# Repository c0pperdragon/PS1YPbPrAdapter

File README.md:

# PS1 YPbPr Adapter

## Goal

To get the best possible image quality from the original Sony Playstation, the video signal needs to
be transported in some form of component signal (to avoid the quality loss involved in
encoding/decoding composite video or even S-Video).
The PS1 basically supports RGB output natively, but this standard is not suitable to directly
feed into a mid-range TV. The way to go with current TVs is component video (a.k.a YPbPr) that
has basically the same quality as RGB but uses a different way to encode everything.

There are external converters available for this task, but they add some bulk to the setup 
and additionally need a PS1-to-SCART cable and external power supply.

So, I wanted to build a custom converter circuit that is directly powered from the 
PS1 via its AV-multiout port. By directly using the available Lum output (part of the S-Video signal)
which already carries the necessary sync information, I only had to construct the 
Pb and Pr signals from the R,G,B outputs.

## Implementation

The circuit consists of three main parts:
- Input: Bring the R,G,B signals to a defined DC level
- Create Pb, Pr: Use a resistor matrix and an OpAmp to generate an inverted luminance signal 
    which will then be added to each of the R and B signals to get the Pb and Pr levels.
- Output: Amplify the signals for transmission over the output cable. 

The main problem with the whole project was to get/create a plug for the AV multi-out 
that not only carries the RGB signals, but also the Lum, the power and Audio signals
as well. None of the existing cables in the market actually does that.

None except this one: The SCPH-1160 was a small adapter box from Sony intended to break out
audio and composite video while providing an additional multi-out for additional stuff to
be connected. So all 12 pins of the multi-out and even the shielding ground are connected
through. Even better, the cable itself can be detached from the circuit board to
easily connect some prototyping circuit. With some luck I could find a second hand
part on e-bay.

After some serious board layout work, I was able to squeeze my whole electronics 
into the case of the SCPH-1160, and could even use the original RCA connectors
to now output the YPbPr signal instead of AV. I added a 3.5mm stereo jack to make the
device complete.

## Results

I was playing mainly "CastleVania: Symphony of the Night" to test the setup
and the video and sound quality is very good on my Samsung UE22K5000AK.
This TV seems to have special support for game consoles and handles the 280p signal
(I have a PAL version of the Playstation) very well. The pixels are pretty sharp,
there is no noise in solid color regions and I can not notice any lag whatsoever.
The only bad thing is that the image seems to have a slight flicker of the 
luminance when the game scrolls and the screen is mainly half-bright. I have
not yet figured out if this is a problem of the Lum output of the PS1 or caused by 
my circuit. Nevertheless I am very happy with the image quality now.
Have a look at the gallery for a test image.

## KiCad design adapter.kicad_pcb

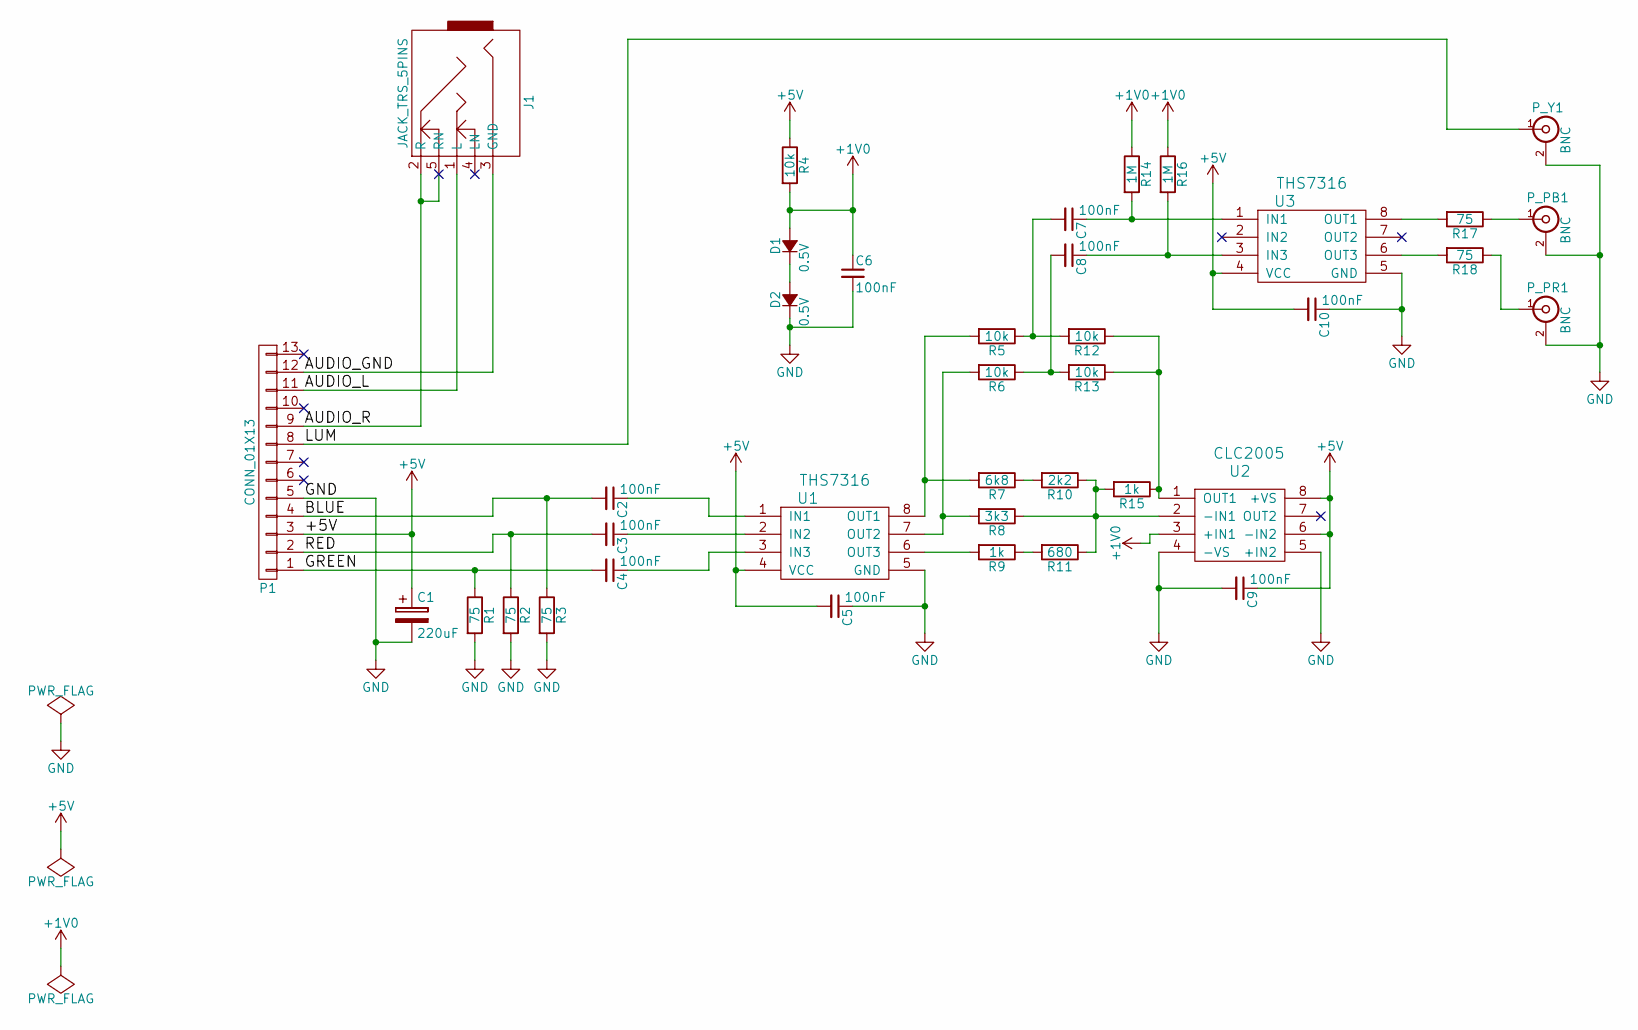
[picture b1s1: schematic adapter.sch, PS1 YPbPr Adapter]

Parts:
C1: 220uF; CP_Radial_D8.0mm_P3.80mm
C2, C3, C4, C5, C6, C7, C8, C9, C10: 100nF; C_0805_HandSoldering
D1, D2: 0.5V; D_A-405_P7.62mm_Horizontal
J1: JACK_TRS_5PINS; Stereo_Jack_3.5mm_Switch_Ledino_KB3SPRS
P1: CONN_01X13; Pin_Header_Straight_1x13_Pitch2.00mm
P_PB1: BNC; AK300-2
P_PR1: BNC; AK300-2
P_Y1: BNC; AK300-2
R1, R2, R3: 75; R_Axial_DIN0207_L6.3mm_D2.5mm_P7.62mm_Horizontal
R4, R5, R6, R12, R13: 10k; R_0805_HandSoldering
R7: 6k8; R_0805_HandSoldering
R8: 3k3; R_0805_HandSoldering
R9, R15: 1k; R_0805_HandSoldering
R10: 2k2; R_0805_HandSoldering
R11: 680; R_0805_HandSoldering
R14, R16: 1M; R_Axial_DIN0309_L9.0mm_D3.2mm_P20.32mm_Horizontal
R17, R18: 75; R_Axial_DIN0207_L6.3mm_D2.5mm_P15.24mm_Horizontal
U1, U3: THS7316; SO-8_5.3x6.2mm_Pitch1.27mm
U2: CLC2005; SO-8_5.3x6.2mm_Pitch1.27mm

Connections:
+1V0: C6.1, D1.2 (A), R4.2, R14.1, R16.1, U2.3 (+IN1)
+5V: C1.1, C5.2, C9.1, C10.2, P1.3, R4.1, U1.4 (VCC), U2.6 (-IN2), U2.8 (+VS), U3.4 (VCC)
/AUDIO_GND: J1.3 (GND), P1.12
/AUDIO_L: J1.1 (L), P1.11
/AUDIO_R: J1.2 (R), J1.5 (RN), P1.9
/BLUE: C2.2, P1.4, R3.1
/GREEN: C4.2, P1.1, R1.1
/LUM: P1.8, P_Y1.1 (In)
/RED: C3.2, P1.2, R2.1
GND: C1.2, C5.1, C6.2, C9.2, C10.1, D2.1 (K), P1.5, P_PB1.2 (Ext), P_PR1.2 (Ext), P_Y1.2 (Ext), R1.2, R2.2, R3.2, U1.5 (GND), U2.4 (-VS), U2.5 (+IN2), U3.5 (GND)
unnamed: C2.1, U1.1 (IN1)
unnamed: C3.1, U1.2 (IN2)
unnamed: C4.1, U1.3 (IN3)
unnamed: C7.1, R14.2, U3.1 (IN1)
unnamed: C7.2, R5.1, R12.2
unnamed: C8.1, R16.2, U3.3 (IN3)
unnamed: C8.2, R6.1, R13.2
unnamed: D1.1 (K), D2.2 (A)
unnamed: P_PB1.1 (In), R17.1
unnamed: P_PR1.1 (In), R18.1
unnamed: R5.2, R7.2, U1.8 (OUT1)
unnamed: R6.2, R8.2, U1.7 (OUT2)
unnamed: R9.2, U1.6 (OUT3)
unnamed: R8.1, R10.1, R11.1, R15.2, U2.2 (-IN1)
unnamed: R7.1, R10.2
unnamed: R9.1, R11.2
unnamed: R12.1, R13.1, R15.1, U2.1 (OUT1)
unnamed: R17.2, U3.8 (OUT1)
unnamed: R18.2, U3.6 (OUT3)

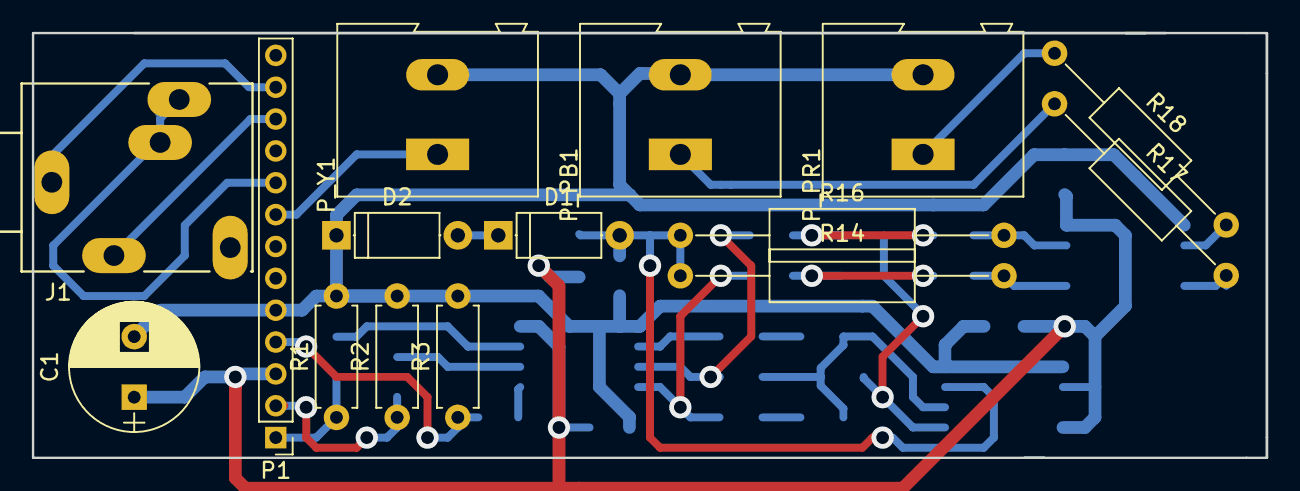
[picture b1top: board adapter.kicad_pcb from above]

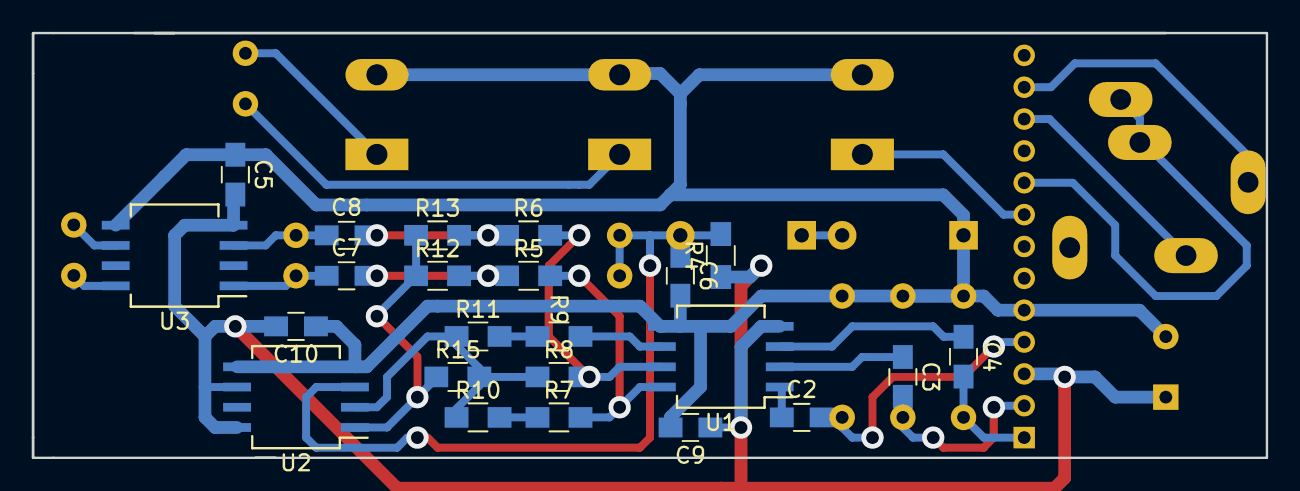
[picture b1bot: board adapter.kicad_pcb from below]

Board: 2 copper layers, 77.5 x 26.7 mm, 38 parts (23 on the bottom side), 29 nets.

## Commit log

2017-09-18 :circus_tent: Added .gitattributes & .gitignore files
2017-09-18 Initial check-in
2017-09-19 gallery pictures
